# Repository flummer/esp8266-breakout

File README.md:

# ESP8266 Breakout Board

This is a simple breakout board for the ESP8266-12E/F modules, designed to be easy to use with the [WLED Project](https://kno.wled.ge/) and also possible to solder without too much trouble using a regular soldering iron.

It's relatively bare bone and only have the minimum required, though 2 buttons are included to make it easier to reset and flash the controller. The buttons can be omitted and simply shorted when programming, as they are not needed for running WLED.

## BOM

The [Interactive HTML BOM](https://html-preview.github.io/?url=https://github.com/flummer/esp8266-breakout/blob/main/bom/ibom.html) is included for assistance with assembly.

## Designed in KiCad v9

To open the project, you will need to install v9 or a recent nightly build, KiCad v8 or earlier won't open this design directly.

[Electronics schematics as a PDF file](https://github.com/flummer/esp8266-breakout/blob/main/ESP8266-Breakout-Schematic.pdf) is also included for reference.

You can also have a look at the design using [KiCanvas](https://kicanvas.org/?github=https%3A%2F%2Fgithub.com%2Fflummer%2Fesp8266-breakout).

## License

The hardware design of the `main` branch of this repository is released under the following license:

* the "Creative Commons Attribution-ShareAlike 4.0 International License"
  (CC BY-SA 4.0) full text of this license is included in the LICENSE file
  and a copy can also be found at
  [http://creativecommons.org/licenses/by-sa/4.0/](http://creativecommons.org/licenses/by-sa/4.0/)

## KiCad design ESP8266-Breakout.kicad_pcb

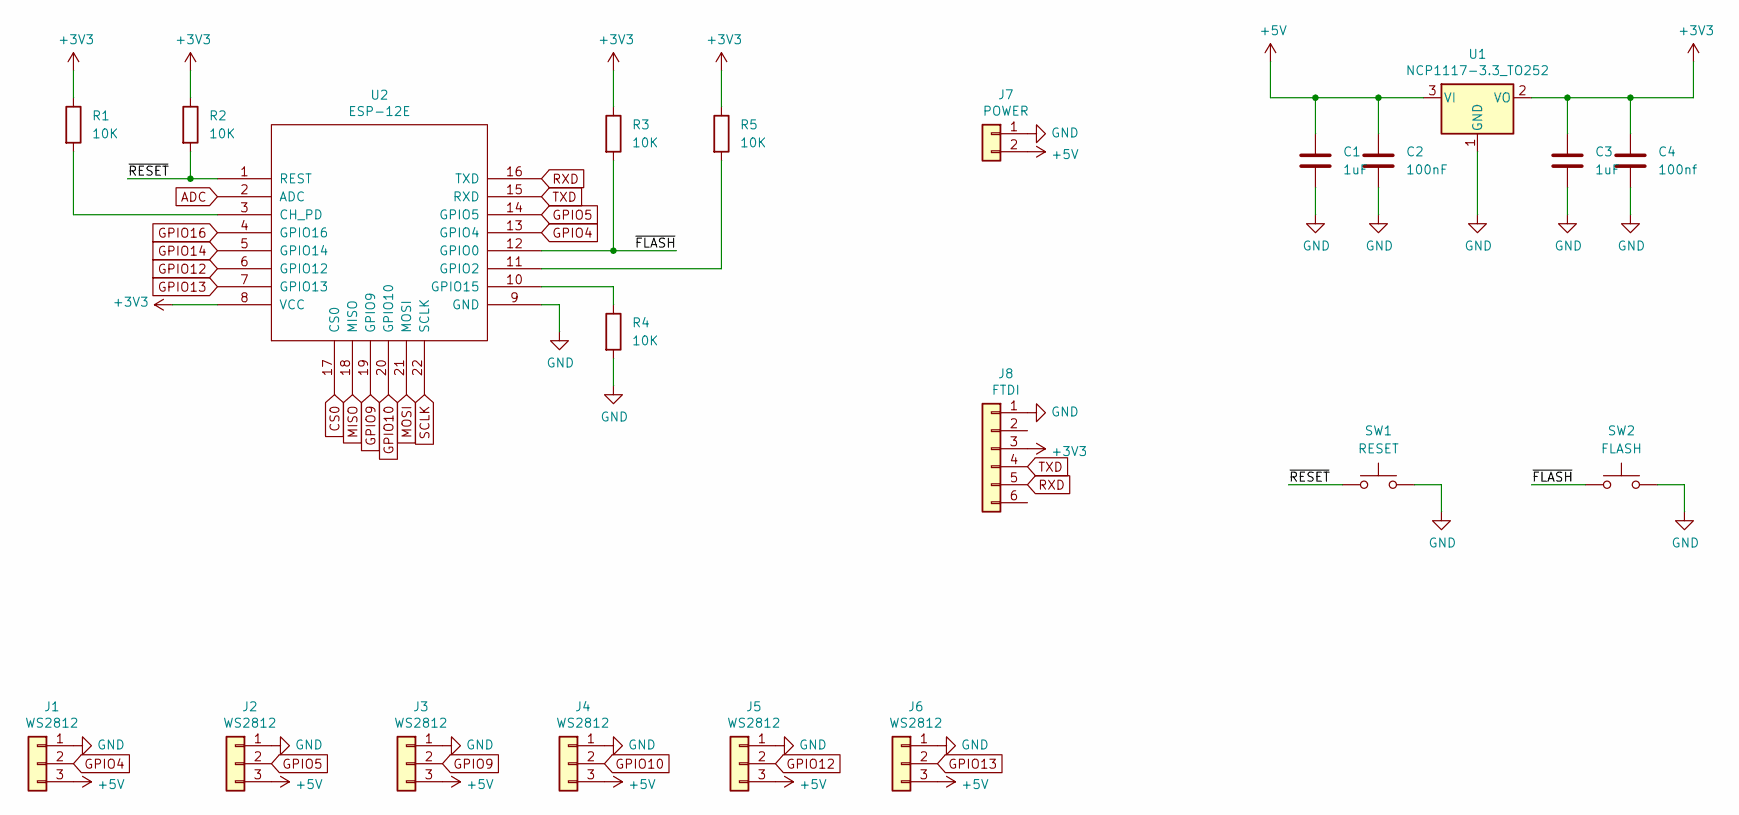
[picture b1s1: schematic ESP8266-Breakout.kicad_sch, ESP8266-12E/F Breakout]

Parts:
C1, C3: 1uF; C_0805_2012Metric_Pad1.18x1.45mm_HandSolder
C2: 100nF; C_0805_2012Metric_Pad1.18x1.45mm_HandSolder
C4: 100nf; C_0805_2012Metric_Pad1.18x1.45mm_HandSolder
J1, J2, J3, J4, J5, J6: WS2812; PinHeader_1x03_P2.54mm_Vertical
J7: POWER; PinHeader_1x02_P2.54mm_Vertical
J8: FTDI; PinHeader_1x06_P2.54mm_Vertical
R1, R2, R3, R4, R5: 10K; R_0805_2012Metric_Pad1.20x1.40mm_HandSolder
SW1: RESET; SW_SPST_TL3342
SW2: FLASH; SW_SPST_TL3342
U1: NCP1117-3.3_TO252; TO-252-2
U2: ESP-12E; ESP-12E_SMD

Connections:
+3V3: C3.1, C4.1, J8.3, R1.1, R2.1, R3.1, R5.1, U1.2 (VO), U2.8 (VCC)
+5V: C1.1, C2.1, J1.3, J2.3, J3.3, J4.3, J5.3, J6.3, J7.2, U1.3 (VI)
/~FLASH: R3.2, SW2.1, U2.12 (GPIO0)
/~RESET: R2.2, SW1.1, U2.1 (REST)
ADC: U2.2 (ADC)
CS0: U2.17 (CS0)
GND: C1.2, C2.2, C3.2, C4.2, J1.1, J2.1, J3.1, J4.1, J5.1, J6.1, J7.1, J8.1, R4.2, SW1.2, SW2.2, U1.1 (GND), U2.9 (GND)
GPIO4: J1.2, U2.13 (GPIO4)
GPIO5: J2.2, U2.14 (GPIO5)
GPIO9: J3.2, U2.19 (GPIO9)
GPIO10: J4.2, U2.20 (GPIO10)
GPIO12: J5.2, U2.6 (GPIO12)
GPIO13: J6.2, U2.7 (GPIO13)
GPIO14: U2.5 (GPIO14)
GPIO16: U2.4 (GPIO16)
MISO: U2.18 (MISO)
MOSI: U2.21 (MOSI)
unnamed: R1.2, U2.3 (CH_PD)
unnamed: R5.2, U2.11 (GPIO2)
unnamed: R4.1, U2.10 (GPIO15)
RXD: J8.5, U2.16 (TXD)
SCLK: U2.22 (SCLK)
TXD: J8.4, U2.15 (RXD)

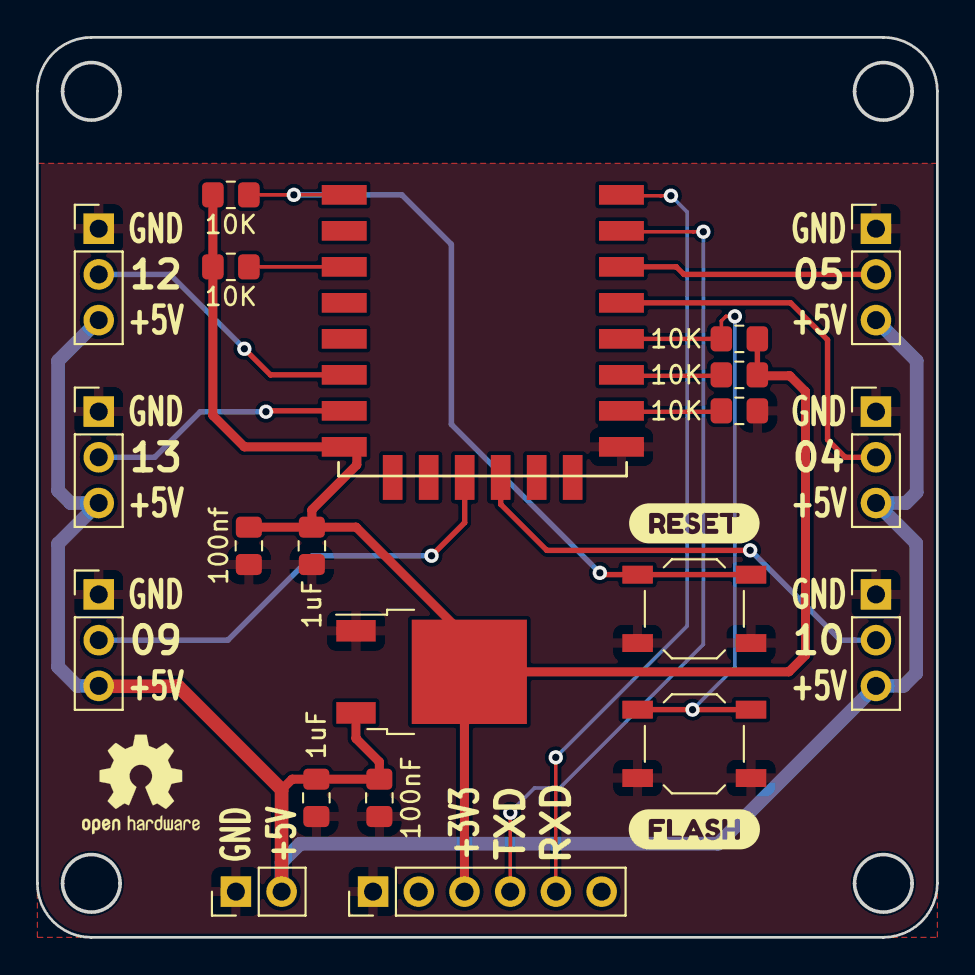
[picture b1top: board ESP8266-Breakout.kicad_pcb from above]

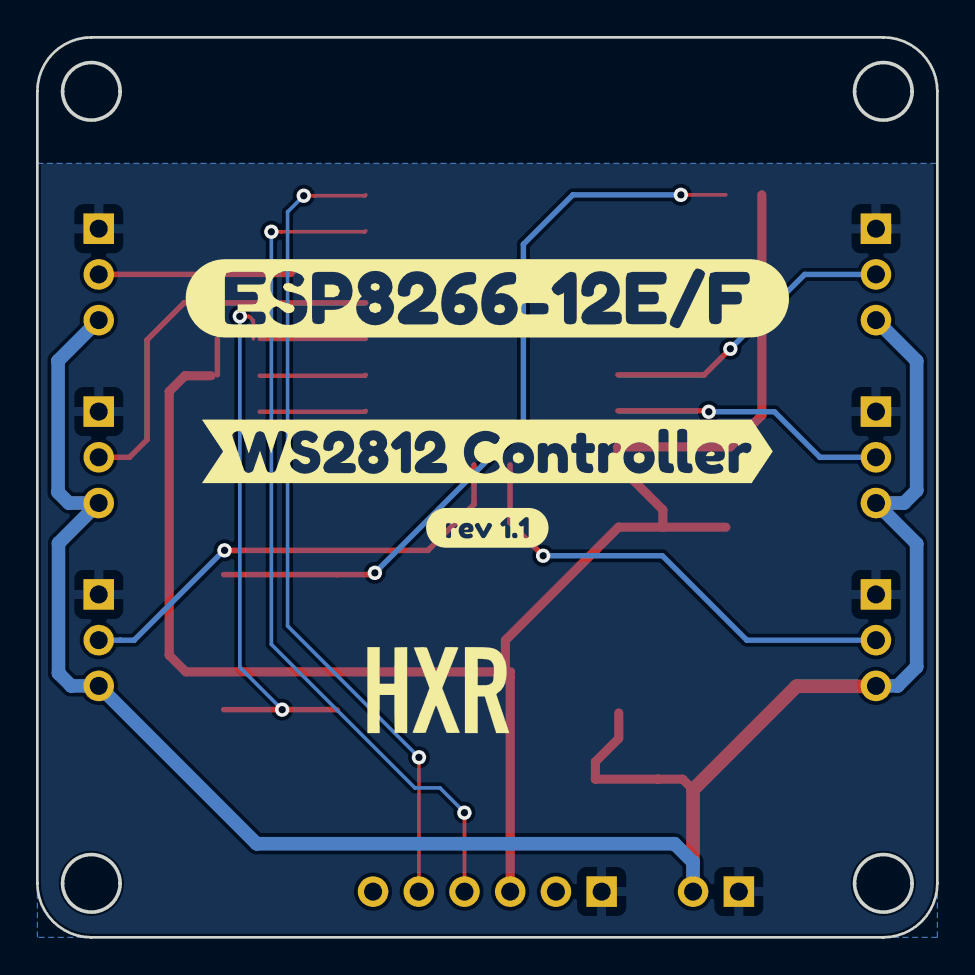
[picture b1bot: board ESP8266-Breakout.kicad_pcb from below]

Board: 2 copper layers, 50.0 x 50.0 mm, 26 parts (3 on the bottom side), 16 nets.

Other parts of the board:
kibuzzard-62A653A7: G***; kibuzzard-62A653A7
kibuzzard-62A6539A: G***; kibuzzard-62A6539A
kibuzzard-62A6554C: G***; kibuzzard-62A6554C
kibuzzard-62A6557D: G***; kibuzzard-62A6557D
kibuzzard-62A65508: G***; kibuzzard-62A65508

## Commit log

2025-04-15 Initial version
    This matches v.1.1 of the project
